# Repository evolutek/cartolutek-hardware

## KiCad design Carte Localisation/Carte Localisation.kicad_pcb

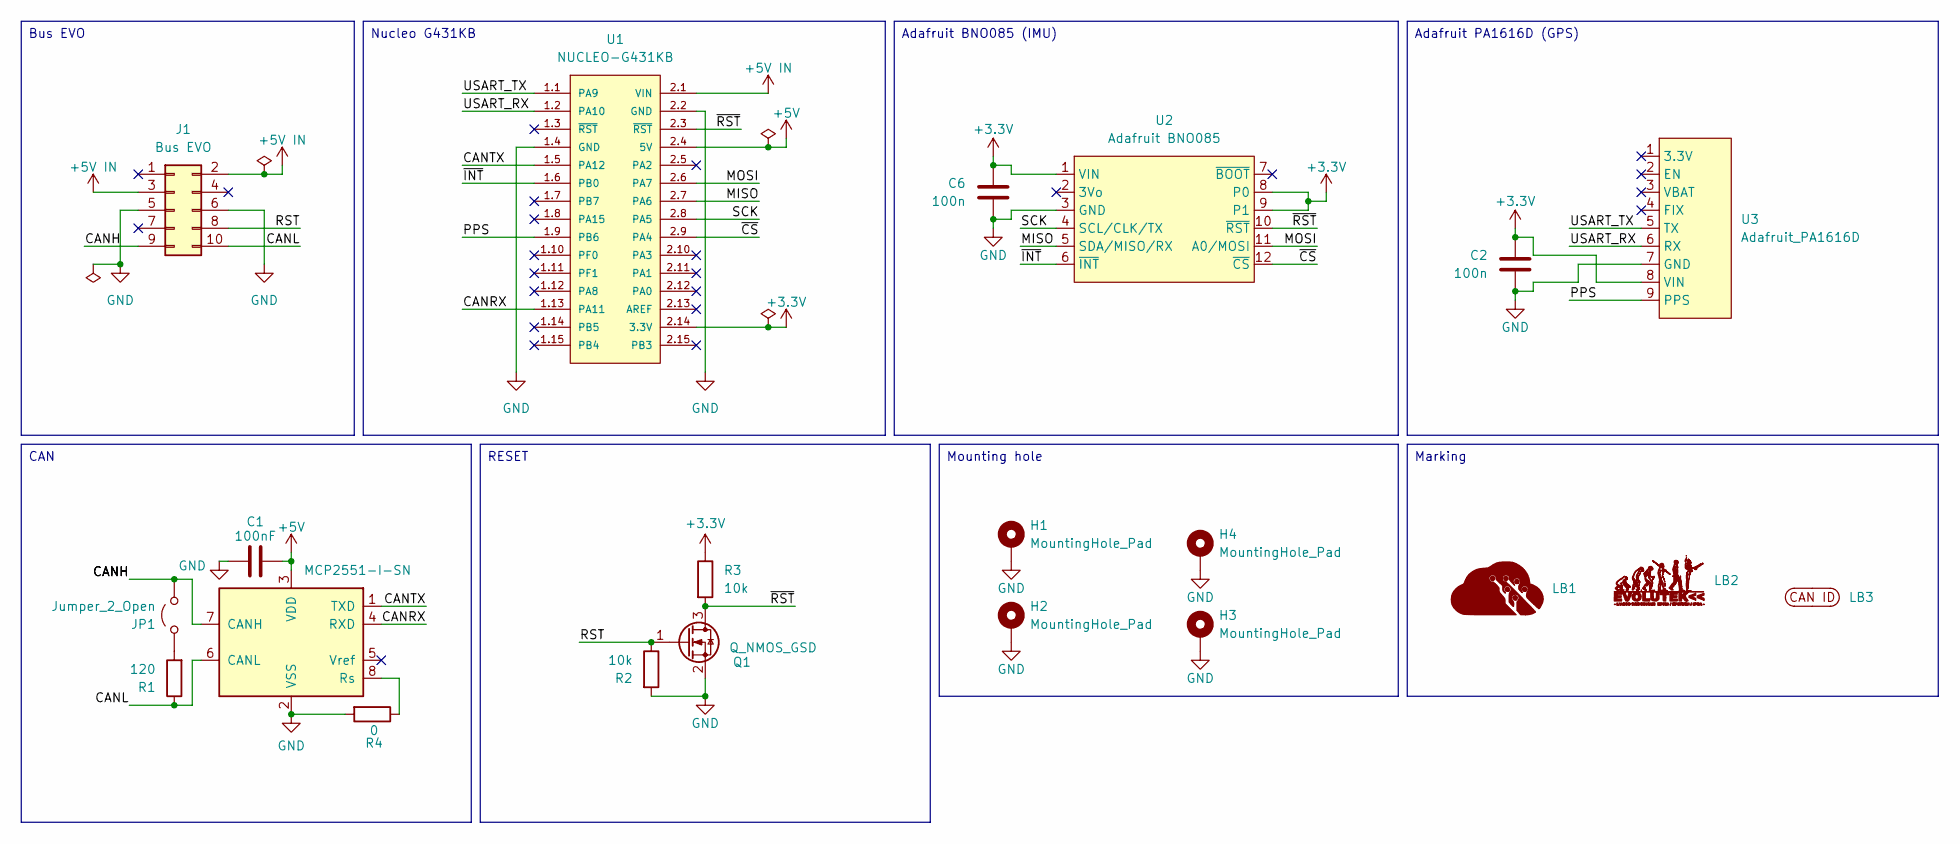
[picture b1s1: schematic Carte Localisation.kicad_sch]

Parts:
C1: 100nF; C_0603_1608Metric
C2, C6: 100n; C_0603_1608Metric
H1, H2, H3, H4: MountingHole_Pad; MountingHole_3.2mm_M3_Pad_Via
J1: Bus EVO; 690367281076
JP1: Jumper_2_Open; PinHeader_1x02_P2.54mm_Vertical
LB1: LOGO; Logo Aisler Min
LB2: LOGO; logo-evo-min
LB3: CAN ID Label
Q1: Q_NMOS_GSD; SOT-23
R1: 120; R_0603_1608Metric
R2, R3: 10k; R_0603_1608Metric
R4: 0; R_0603_1608Metric
U1: NUCLEO-G431KB; MODULE_NUCLEO-32
U2: Adafruit BNO085
U3: Adafruit_PA1616D; Adafruit PA1616D
U4: MCP2551-I-SN; SOIC-8_3.9x4.9mm_P1.27mm

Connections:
+3.3V: C2.2, C6.2, R3.1, U1.2.14 (3.3V), U2.1 (VIN), U2.8 (P0), U2.9 (P1), U3.8 (VIN)
+5V: C1.1, U1.2.4 (5V), U4.3 (VDD)
+5V IN: J1.2, J1.3, U1.2.1 (VIN)
/CANH: J1.9, JP1.2 (B), U4.7 (CANH)
/CANL: J1.10, R1.1, U4.6 (CANL)
/CANRX: U1.1.13 (PA11), U4.4 (RXD)
/CANTX: U1.1.5 (PA12), U4.1 (TXD)
/MISO: U1.2.7 (PA6), U2.5 (SDA/MISO/RX)
/MOSI: U1.2.6 (PA7), U2.11 (A0/MOSI)
/PPS: U1.1.9 (PB6), U3.9 (PPS)
/RST: J1.8, Q1.1 (G), R2.1
/SCK: U1.2.8 (PA5), U2.4 (SCL/CLK/TX)
/USART_RX: U1.1.2 (PA10), U3.6 (RX)
/USART_TX: U1.1.1 (PA9), U3.5 (TX)
/~CS: U1.2.9 (PA4), U2.12 (~CS)
/~INT: U1.1.6 (PB0), U2.6 (~INT)
/~RST: Q1.3 (D), R3.2, U1.2.3 (~RST), U2.10 (~RST)
GND: C1.2, C2.1, C6.1, H1.1, H2.1, H3.1, H4.1, J1.5, J1.6, Q1.2 (S), R2.2, R4.2, U1.1.4 (GND), U1.2.2 (GND), U2.3 (GND), U3.7 (GND), U4.2 (VSS)
unnamed: JP1.1 (A), R1.2
unnamed: R4.1, U4.8 (Rs)

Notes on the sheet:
Bus EVO
Nucleo G431KB
Marking
RESET
Adafruit PA1616D (GPS)
Adafruit BNO085 (IMU)
CAN
Mounting hole

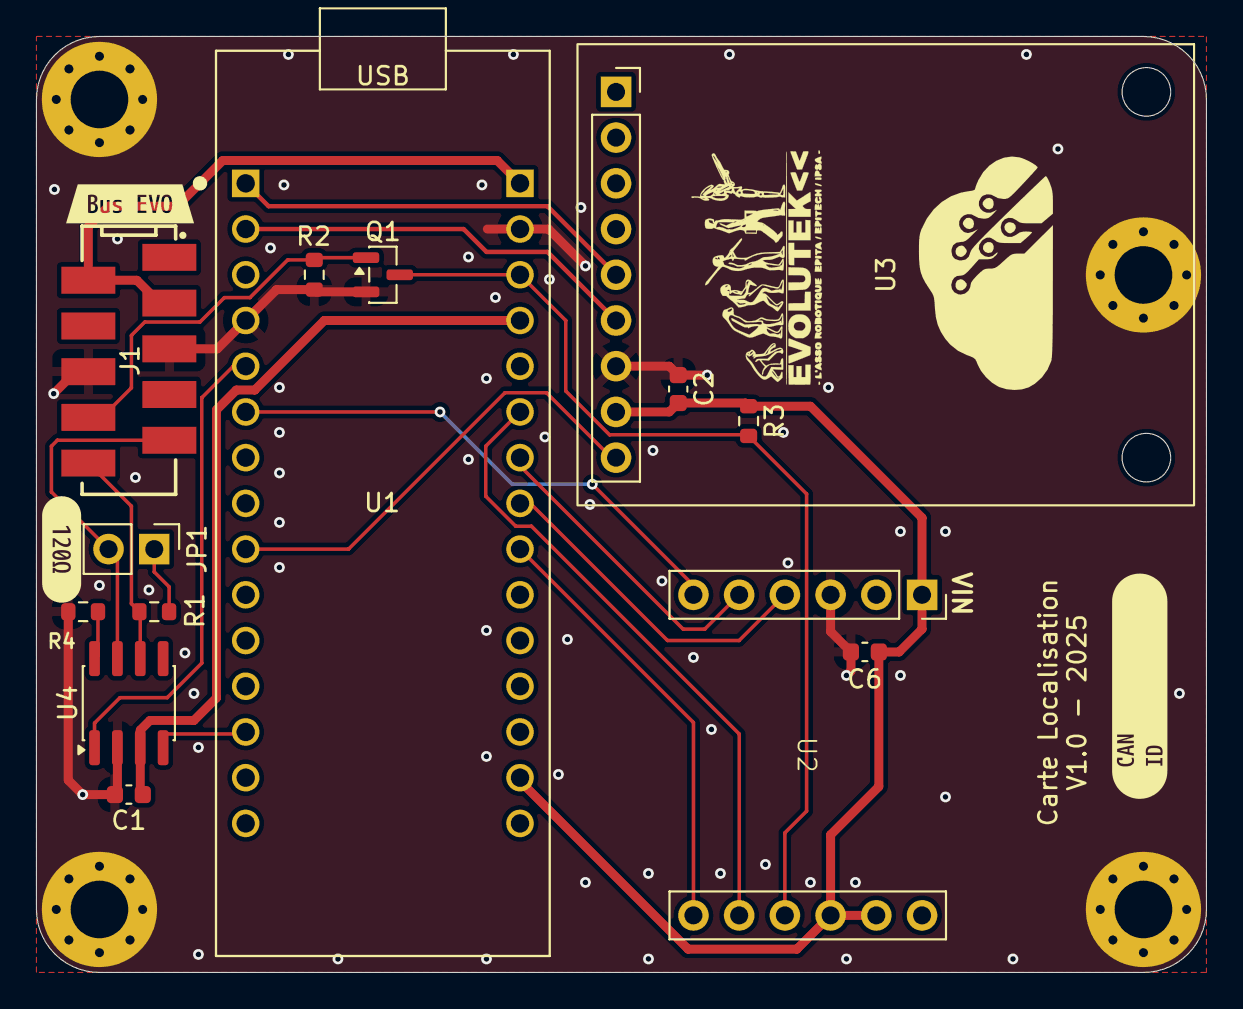
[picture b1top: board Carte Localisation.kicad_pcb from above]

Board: 2 copper layers, 65.0 x 52.0 mm, 23 parts (0 on the bottom side), 20 nets.

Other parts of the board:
kibuzzard-693DE181: G***; kibuzzard-693DE181
kibuzzard-693DE208: G***; kibuzzard-693DE208

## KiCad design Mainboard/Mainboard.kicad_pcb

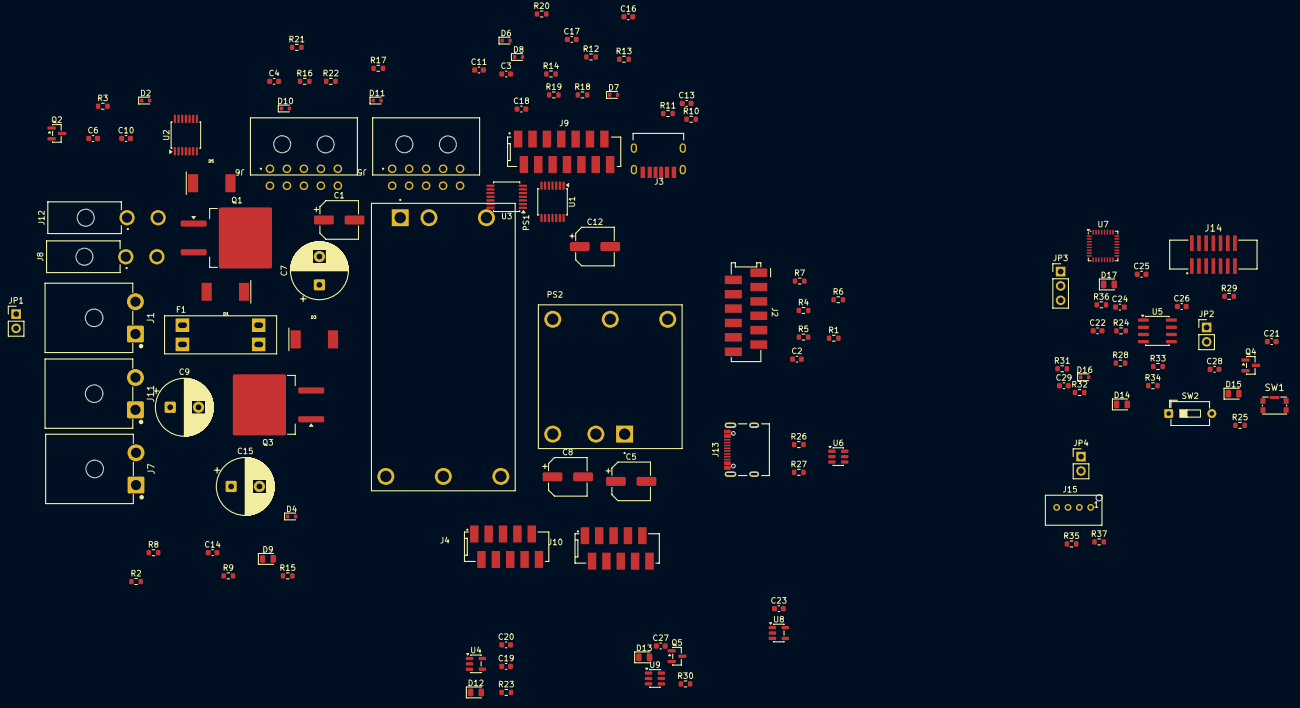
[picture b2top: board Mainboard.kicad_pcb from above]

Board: 2 copper layers, 121 parts (0 on the bottom side), 80 nets, no tracks yet.

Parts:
C1, C5, C8, C12: 100uF; CP_Elec_6.3x7.7
C2: 22nF; C_0603_1608Metric
C3, C4, C10, C11, C16, C17, C18, C21, C22, C23, C25, C26, C27: 100nF; C_0603_1608Metric
C6, C14, C19, C20: 1uF; C_0603_1608Metric
C7, C9, C15: 470uF; CP_Radial_D10.0mm_P5.00mm
C13, C24, C29: 10uF; C_0603_1608Metric
C28: 10nF; C_0603_1608Metric
D1, D3, D5: D; DO-214AB
D2, D4: 15V; D_SOD-523
D6, D7, D8, D10, D11, D16: 3V; D_SOD-523
D9, D12: RED; LED_0805_2012Metric
D13, D14, D15: YELLOW; LED_0805_2012Metric
D17: GREEN; LED_0805_2012Metric
F1: 50A; FUSE_3557-2
J1: BATT; 657002140101
J2: Computer Interface; J_Wurth_WR-MM_690367281276
J3: USB_C_Receptacle_PowerOnly_6P; GCT_USB4125-GF-A_REVA2
J4, J10: Bus EVO; 690367281076
J5, J6: Hoop Interface Front; 66201021022
J7, J11: MOTORS; 657002140101
J8, J12: AUX; 649002227222
J9: UI Interface; 690367281476
J13: USB_C_Receptacle_USB2.0_16P; 629722000214
J14: STLINK; 62701420621
J15: I2C; B04B-PASK
JP1, JP2, JP4: Jumper_2_Small_Open; PinHeader_1x02_P2.54mm_Vertical
JP3: Jumper_3_Bridged12; PinHeader_1x03_P2.54mm_Vertical
PS1: TEN_40-4812WIE; TRACO_CONV_TEN
PS2: THL_20-2411WI; TRACO_CONV_THL
Q1, Q3: Q_PMOS_GDS; TO-263-2
Q2: Q_NMOS_GSD 60V; SOT-23
Q4, Q5: NMOS; SOT-23
R1, R2, R5, R6, R7, R8, R10, R11, R12, R13, R14, R21, R22, R25, R29, R31: 10k; R_0603_1608Metric
R3, R9, R16, R17, R18, R19, R20: 33k; R_0603_1608Metric
R4, R15: 22k; R_0603_1608Metric
R23, R30, R32, R33, R34, R36: 510; R_0603_1608Metric
R24: 120; R_0603_1608Metric
R26, R27: 5.1k; R_0603_1608Metric
R28: 0; R_0603_1608Metric
R35, R37: 4.7k; R_0603_1608Metric
SW1: 435431019840
SW2: SW_DIP_x01; SW_DIP_SPSTx01_Slide_6.7x4.1mm_W7.62mm_P2.54mm_LowProfile
U1, U2, U3: SN74LVTH125; TSSOP-14_4.4x5mm_P0.65mm
U4: NCP718xSN330; SOT-23-5
U5: MCP2551-I-SN; SOIC-8_3.9x4.9mm_P1.27mm
U6: WE-TVS-82400102; SOT-23-6
U7: STM32G491KEUx; QFN-32-1EP_5x5mm_P0.5mm_EP3.45x3.45mm-Without thermal pad
U8: SN74LVC1G32; SOT-23-5
U9: SN74LVC1G11; SOT-23-6

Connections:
+3.3V: C3.1, C4.1, C11.1, C20.1, C23.1, C24.1, C25.1, C26.1, C27.1, C28.1, D12.2 (A), J14.3, JP3.3 (B), R25.1, R30.1, R35.1, R37.1, SW2.1, U1.14 (VCC), U2.14 (VCC), U3.14 (VCC), U4.5 (OUT), U7.1 (VDD), U7.15 (VDDA), U7.17 (VDD), U8.5 (VCC), U9.5 (VCC)
+5V: C13.1, C19.1, C22.1, J2.1, J2.2, J3.A9 (VBUS), J3.B9 (VBUS), J4.2, J4.3, J10.2, J10.3, JP4.1 (A), R10.2, R11.2, U4.1 (IN), U4.3 (EN), U5.3 (VDD)
+5VT: C12.1, PS2.3 (+VOUT)
+12V: C5.1, C8.1, J4.1, J5.7, J6.7, J9.2, J10.1, PS1.4 (+VOUT), PS2.1 (+VIN(VCC))
/Interfaces/AUTO_MODE_ENABLE: D14.2 (A), U1.5 (2A), U7.12 (PA7)
/Interfaces/AUTO_MODE_ENABLE_U: J9.8, U1.6 (2Y)
/Interfaces/AUTO_MODE_SWITCH: C17.1, D7.1 (K), R13.1, R19.1, U7.26 (PB3)
/Interfaces/BUZZER: U3.2 (1A), U7.9 (PA4)
/Interfaces/BUZZER_U: J9.12, U3.3 (1Y)
/Interfaces/CAMERA_SYNC_C: C2.1, J2.7, R4.1, U2.12 (4A)
/Interfaces/CAMERA_SYNC_H: J5.5, J6.5, U2.11 (4Y)
/Interfaces/CANH: J2.11, J4.9, J10.9, JP2.1 (A), U5.7 (CANH)
/Interfaces/CANL: J2.12, J4.10, J10.10, R24.2, U5.6 (CANL)
/Interfaces/EMERGENCY_STOP: D13.1 (K), J4.7, J10.7, Q5.1 (D), U7.6 (PA1)
/Interfaces/EMERGENCY_SWITCH_BACK: D11.1 (K), R17.2, R22.1, U9.3 (B)
/Interfaces/EMERGENCY_SWITCH_FRONT: D10.1 (K), R16.2, R21.1, U9.1 (A)
/Interfaces/GREEN_LED_C: J2.5, R5.1, U1.12 (4A)
/Interfaces/GREEN_LED_U: J9.10, U1.11 (4Y)
/Interfaces/HEADLIGHTS: U3.12 (4A), U7.10 (PA5)
/Interfaces/HEADLIGHTS_H: J5.8, J6.8, U3.11 (4Y)
/Interfaces/LEDSTRIP_BACK: U2.9 (3A), U7.30 (PB7)
/Interfaces/LEDSTRIP_BACK_H: J6.4, U2.8 (3Y)
/Interfaces/LEDSTRIP_FRONT: U2.5 (2A), U7.27 (PB4)
/Interfaces/LEDSTRIP_FRONT_H: J5.4, U2.6 (2Y)
/Interfaces/MOTOR_POWER_ENABLE: D15.2 (A), JP3.2 (C), Q2.1 (G), U1.2 (1A)
/Interfaces/MOTOR_POWER_ENABLE_U: J9.6, U1.3 (1Y)
/Interfaces/MOTOR_POWER_SWITCH: C16.1, D6.1 (K), R12.1, R18.1, U7.13 (PB0)
/Interfaces/RED_LED_C: J2.6, R6.1, U1.9 (3A)
/Interfaces/RED_LED_U: J9.11, U1.8 (3Y)
/Interfaces/RESET_SOFT: J2.9, R1.1, U8.2 (B)
/Interfaces/RESET_SWITCH: C18.1, D8.1 (K), R14.1, R20.1, U8.1 (A)
/Interfaces/SCL: J9.14, J15.3, R35.2, U7.19 (PA9)
/Interfaces/SDA: J9.13, J15.2, R37.2, U7.18 (PA8)
/Interfaces/WARNING_LIGHTS: U2.2 (1A), U7.25 (PA15)
/Interfaces/WARNING_LIGHTS_H: J5.9, J6.9, U2.3 (1Y)
/Interfaces/~EMERGENCY_STOP_SOFT: J2.8, R7.1, U9.6 (C)
/Interfaces/~POWER_SWITCH: C6.2, D2.2 (A), J9.3, JP1.2 (B), Q1.1 (G), R2.2, R3.1
/Logic/BATTERY_SENSE: C29.1, D16.1 (K), R31.2, R32.1, U7.5 (PA0)
/Logic/CAN_RX: U5.4 (RXD), U7.28 (PB5)
/Logic/CAN_TX: U5.1 (TXD), U7.29 (PB6)
/Logic/D_N: J13.A7 (D-), J13.B7 (D-), U6.1
/Logic/D_P: J13.A6 (D+), J13.B6 (D+), U6.3
/Logic/RST: J2.10, J4.8, J10.8, Q4.2 (G), U8.4 (S)
/Logic/STATUS: D17.2 (A), U7.20 (PA10)
/Logic/SWCLK: J14.6, U7.24 (PA14)
/Logic/SWDIO: J14.4, U7.23 (PA13)
/Logic/USB_N: U6.6, U7.21 (PA11)
/Logic/USB_P: U6.4, U7.22 (PA12)
/Logic/VCP_RX: J14.13, U7.8 (PA3)
/Logic/VCP_TX: J14.14, U7.7 (PA2)
/Logic/~RST: C21.1, J14.12, Q4.1 (D), R25.2, SW1.4, U7.4 (PG10)
GND: C1.2, C2.2, C3.2, C4.2, C5.2, C7.2, C8.2, C9.2, C10.2, C11.2, C12.2, C13.2, C15.2, C16.2, C17.2, C18.2, C19.2, C20.2, C21.2, C22.2, C23.2, C24.2, C25.2, C26.2, C27.2, C28.2, C29.2, D1.2 (A), D6.2 (A), D7.2 (A), D8.2 (A), D10.2 (A), D11.2 (A), D16.2 (A), J1.2, J2.3, J2.4, J3.A12 (GND), J3.B12 (GND), J3.S1 (SHIELD), J4.5, J4.6, J5.2, J5.3, J6.2, J6.3, J7.2, J8.2, J9.4, J10.5, J10.6, J11.2, J12.2, J13.A1 (GND), J13.A12 (GND), J13.B1 (GND), J13.B12 (GND), J13.S1 (SHIELD), J14.5, J14.7, J14.11, J15.4, JP1.1 (A), PS1.2 (-VIN(GND)), PS1.5 (-VOUT), PS2.2 (-VIN(GND)), PS2.5 (-VOUT), Q2.2 (S), Q4.3 (S), Q5.3 (S), R1.2, R3.2, R4.2, R5.2, R6.2, R7.2, R12.2, R13.2, R14.2, R15.2, R21.2, R22.2, R23.2, R26.1, R27.2, R28.2, R29.2, R32.2, R33.2, R34.2, R36.2, SW1.3, SW1.SH, U1.7 (GND), U2.7 (GND), U3.7 (GND), U4.2 (GND), U5.2 (VSS), U6.2, U7.14 (VSSA), U7.16 (VSS), U7.32 (VSS), U8.3 (GND), U9.2 (GND)
unnamed: C14.2, D4.2 (A), Q3.1 (G), R8.2, R9.1
unnamed: D9.1 (K), R15.1
unnamed: D12.1 (K), R23.1
unnamed: D13.2 (A), R30.2
unnamed: D14.1 (K), R33.1
unnamed: D15.1 (K), R34.1
unnamed: D17.1 (K), R36.1
unnamed: F1.1, J1.1
unnamed: J3.A5 (CC1), R10.1
unnamed: J3.B5 (CC2), R11.1
unnamed: J5.10, R16.1
unnamed: J6.10, R17.1
unnamed: J9.5, R18.2
unnamed: J9.7, R19.2
unnamed: J9.9, R20.2
unnamed: J13.A5 (CC1), R26.2
unnamed: J13.B5 (CC2), R27.1
unnamed: J15.1, JP4.2 (B)
unnamed: JP2.2 (B), R24.1
unnamed: JP3.1 (A), U7.11 (PA6)
unnamed: Q2.3 (D), R9.2
unnamed: Q5.2 (G), U9.4
unnamed: R28.1, U5.8 (Rs)
unnamed: R29.1, SW2.2, U7.31 (PB8)
VBAT: C6.1, C14.1, D1.1 (K), D2.1 (K), D3.1 (K), D4.1 (K), D5.1 (K), F1.2, Q1.3 (S), Q3.3 (S), R2.1, R8.1
VBUS: J13.A4 (VBUS), J13.A9 (VBUS), J13.B4 (VBUS), J13.B9 (VBUS), U6.5
VCC: C1.1, C7.1, C10.1, D3.2 (A), J5.1, J5.6, J6.1, J6.6, J8.1, J9.1, J12.1, PS1.1 (+VIN(VCC)), Q1.2 (D), R31.1
VPP: C9.1, C15.1, D5.2 (A), D9.2 (A), J7.1, J11.1, Q3.2 (D)

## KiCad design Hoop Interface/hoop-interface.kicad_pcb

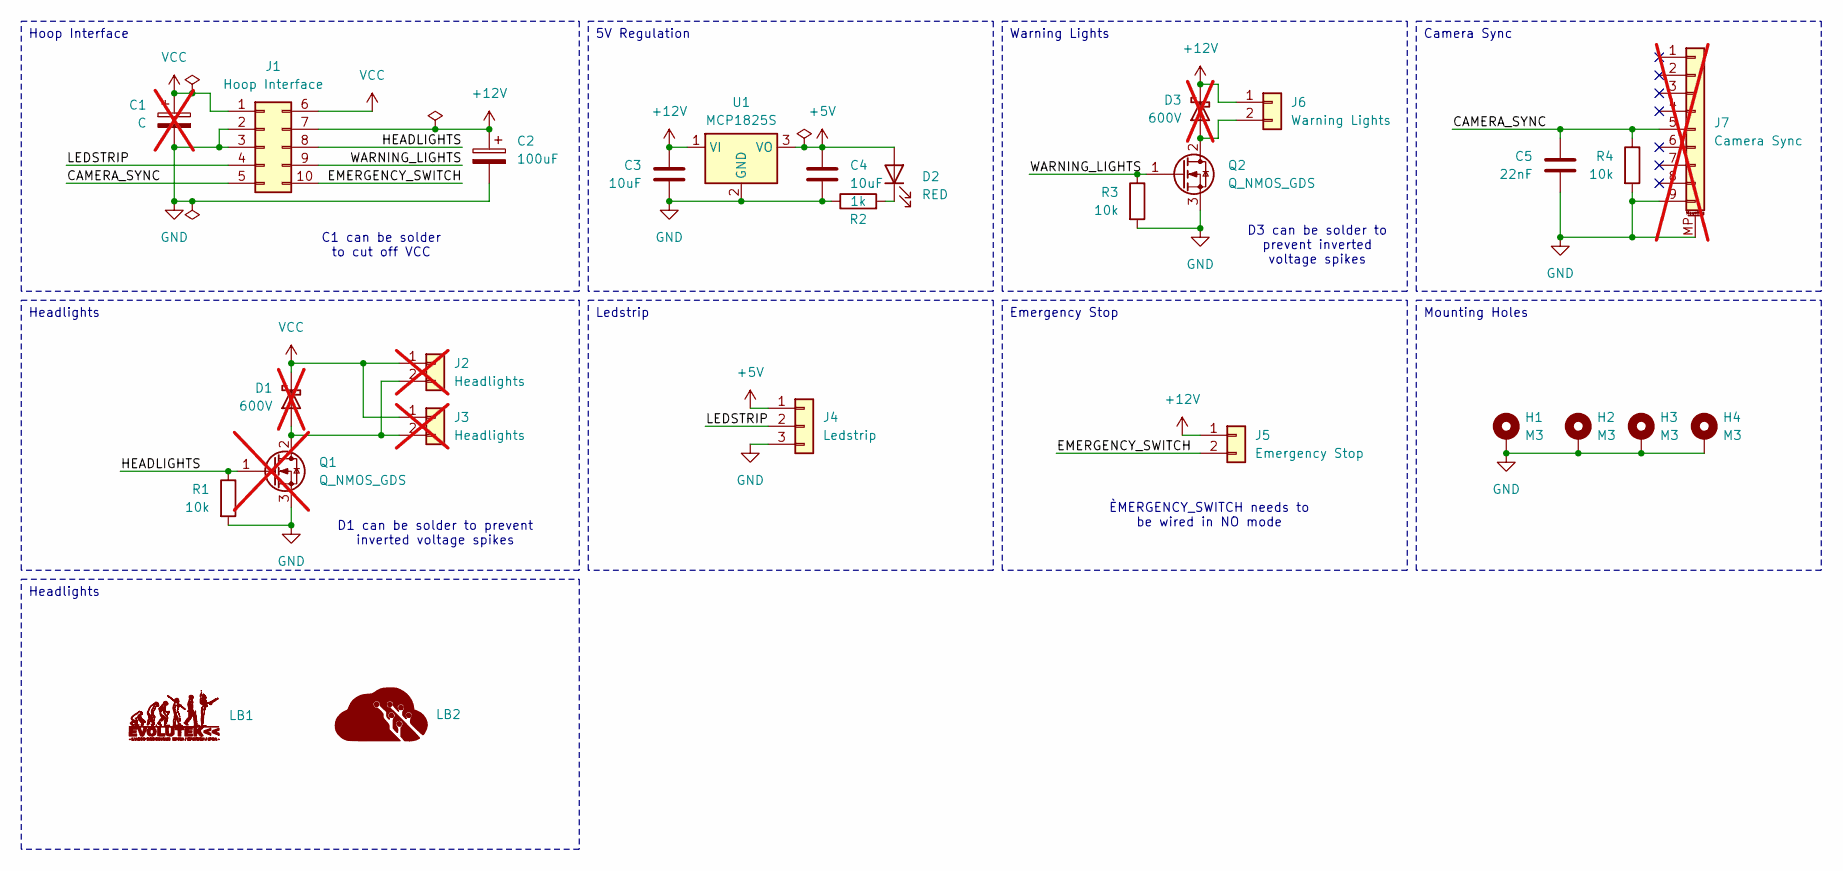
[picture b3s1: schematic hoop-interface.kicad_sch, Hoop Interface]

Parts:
C1: C; CP_Radial_D10.0mm_P5.00mm; not fitted
C2: 100uF; CP_Elec_6.3x7.7
C3, C4: 10uF; C_0603_1608Metric
C5: 22nF; C_0603_1608Metric
D1, D3: 600V; D_SMB; not fitted
D2: RED; LED_0805_2012Metric
H1, H2, H3, H4: M3; MountingHole_3.2mm_M3_Pad_Via
J1: Hoop Interface; 66201021022
J2, J3: Headlights; 66200221022; not fitted
J4: Ledstrip; B03B-PASK
J5: Emergency Stop; 66200221022
J6: Warning Lights; 66200221022
J7: Camera Sync; JST_SH_BM09B-SRSS-TB_1x09-1MP_P1.00mm_Vertical; not fitted
LB1: LOGO; logo-evo-micro
LB2: LOGO; Logo Aisler Micro
Q1: Q_NMOS_GDS; SOT-223-3_TabPin2; not fitted
Q2: Q_NMOS_GDS; SOT-223-3_TabPin2
R1, R3, R4: 10k; R_0603_1608Metric
R2: 1k; R_0603_1608Metric
U1: MCP1825S; SOT-223-3_TabPin2

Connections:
+5V: C4.1, D2.2 (A), J4.1, U1.3 (VO)
+12V: C2.1, C3.1, D3.1 (K), J1.7, J5.1, J6.1, U1.1 (VI)
/CAMERA_SYNC: C5.1, J1.5, J7.5, R4.1
/EMERGENCY_STOP: J1.10, J5.2
/HEADLIGHTS: J1.8, Q1.1 (G), R1.1
/LEDSTRIP: J1.4, J4.2
/WARNING_LIGHTS: J1.9, Q2.1 (G), R3.1
GND: C1.2, C2.2, C3.2, C4.2, C5.2, H1.1, H2.1, H3.1, H4.1, J1.2, J1.3, J4.3, J7.9, J7.MP (MountPin), Q1.3 (S), Q2.3 (S), R1.2, R2.1, R3.2, R4.2, U1.2 (GND)
unnamed: D1.2 (A), J2.2, J3.2, Q1.2 (D)
unnamed: D2.1 (K), R2.2
unnamed: D3.2 (A), J6.2, Q2.2 (D)
VCC: C1.1, D1.1 (K), J1.1, J1.6, J2.1, J3.1

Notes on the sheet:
D1 can be solder to prevent inverted voltage spikes
C1 can be solder to cut off VCC
ÈMERGENCY_SWITCH needs to be wired in NO mode
D3 can be solder to prevent inverted voltage spikes
Emergency Stop
Ledstrip
Warning Lights
5V Regulation
Headlights
Mounting Holes
Hoop Interface
Camera Sync

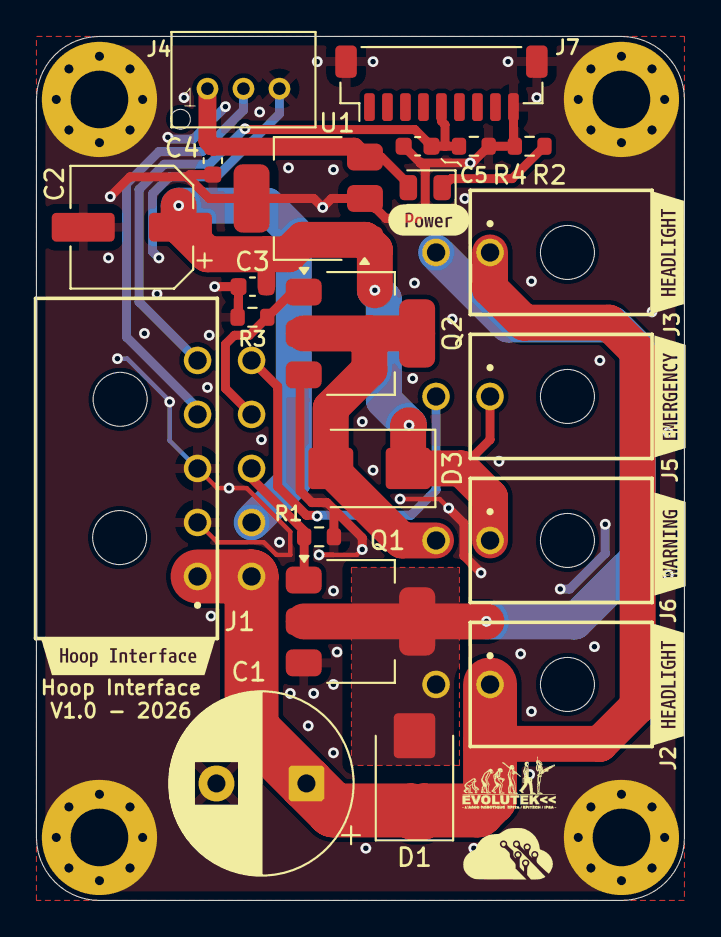
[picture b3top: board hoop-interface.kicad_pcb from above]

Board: 2 copper layers, 36.0 x 48.0 mm, 34 parts (0 on the bottom side), 12 nets.

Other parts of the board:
kibuzzard-69584B36: G***; kibuzzard-69584B36
kibuzzard-69584B63, kibuzzard-69584B63#2: G***; kibuzzard-69584B63
kibuzzard-69584B83: G***; kibuzzard-69584B83
kibuzzard-69584BC4: G***; kibuzzard-69584BC4
kibuzzard-69584D60: G***; kibuzzard-69584D60

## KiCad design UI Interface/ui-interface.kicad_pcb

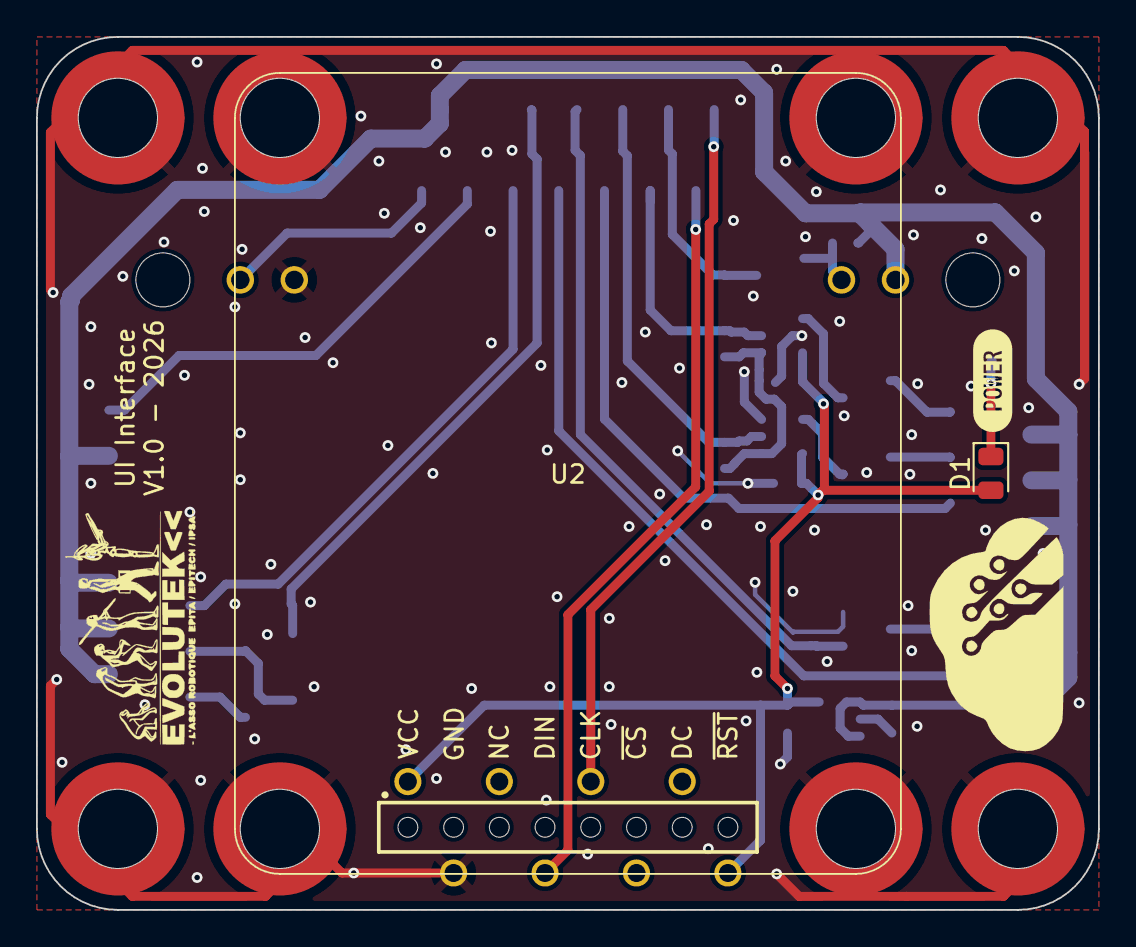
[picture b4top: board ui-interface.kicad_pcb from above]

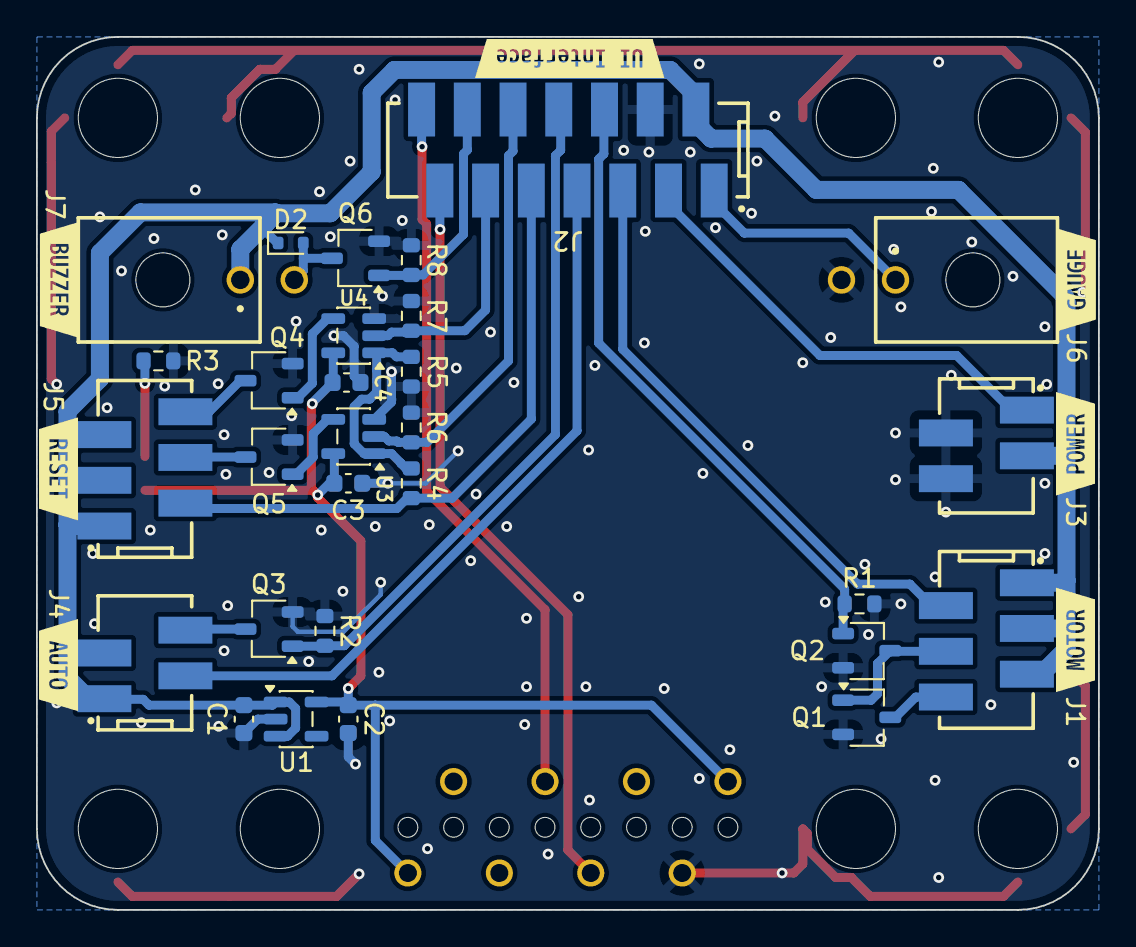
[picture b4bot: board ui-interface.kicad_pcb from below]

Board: 2 copper layers, 59.0 x 48.5 mm, 45 parts (36 on the bottom side), 25 nets.

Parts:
C1, C2: 1uF; C_0603_1608Metric
C3, C4: 100nF; C_0603_1608Metric
D1: RED; LED_0805_2012Metric
D2: D_Schottky; D_SOD-523
H1, H2, H3, H4: M3; WA-SMSI_9774110360
J1: Motor Power Switch; 690367280676
J2: UI Interface; 690367281476
J3: Power Switch; 690367280476
J4: Auto Mode Switch; 690367280476
J5: Reset Switch; 690367280676
J6: Battery Gauge; 66200221022
J7: Buzzer; 66200221022
LB1: LOGO; Logo Aisler Min
LB2: LOGO; logo-evo-min
Q1, Q2, Q3, Q4, Q5, Q6: Q_NMOS_GSD; TSOT-23
R1, R2, R5, R6, R7, R8: 10k; R_0603_1608Metric
R3: 510; R_0603_1608Metric
R4: 33k; R_0603_1608Metric
U1: NCP718xSN330; SOT-23-5
U2: Waveshare_1.5_inch_OLED; Waveshare 1.5 inch with 8mm spacers
U3, U4: SN74LVC1G32; SOT-23-5
kibuzzard-69598A88: G***; kibuzzard-69598A88
kibuzzard-69598DA4: G***; kibuzzard-69598DA4
kibuzzard-695995E5: G***; kibuzzard-695995E5
kibuzzard-695995F9: G***; kibuzzard-695995F9
kibuzzard-6959960F: G***; kibuzzard-6959960F
kibuzzard-69599623: G***; kibuzzard-69599623
kibuzzard-69599634: G***; kibuzzard-69599634
kibuzzard-69599736: G***; kibuzzard-69599736

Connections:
+3.3V: C2.1, C3.1, C4.1, D1.2 (A), U1.5 (OUT), U2.1 (VCC), U2.8 (~RST), U3.5 (VCC), U4.5 (VCC)
+12V: C1.1, D2.1 (K), J1.1, J1.3, J1.5, J2.2, J3.3, J4.1, J4.3, J5.1, J5.3, J5.5, J7.1, U1.1 (IN), U1.3 (EN)
/AUTO_MODE_ENABLE: J2.8, Q3.1 (G), R2.1
/AUTO_MODE_SWITCH: J2.7, J4.2
/BUZZER: J2.12, Q6.1 (G), R8.1
/GREEN: J1.4, Q1.1 (G), Q2.3 (D)
/GREEN_LED: J2.10, R6.1, U3.2 (B)
/MOTOR_POWER_ENABLE: J2.6, Q2.1 (G), R1.1
/MOTOR_POWER_SWITCH: J1.2, J2.5
/RED: J1.6, Q1.3 (D)
/RED_LED: J2.11, R7.1, U4.2 (B)
/RESET: J2.9, J5.2, R4.1
/SCL: J2.14, U2.5 (CLK)
/SDA: J2.13, U2.4 (DIN)
/~POWER_SWITCH: J2.3, J3.1
GND: C1.2, C2.2, C3.2, C4.2, H1.1, H2.1, H3.1, H4.1, J2.4, J3.2, J3.4, J6.2, Q1.2 (S), Q2.2 (S), Q3.2 (S), Q4.2 (S), Q5.2 (S), Q6.2 (S), R1.2, R2.2, R3.2, R5.2, R6.2, R7.2, R8.2, U1.2 (GND), U2.2 (GND), U2.MP, U3.3 (GND), U4.3 (GND)
unnamed: D1.1 (K), R3.1
unnamed: D2.2 (A), J7.2, Q6.3 (D)
unnamed: J4.4, Q3.3 (D)
unnamed: J5.4, Q5.3 (D)
unnamed: J5.6, Q4.3 (D)
unnamed: Q4.1 (G), U4.4 (S)
unnamed: Q5.1 (G), U3.4 (S)
unnamed: R4.2, R5.1, U3.1 (A), U4.1 (A)
VCC: J2.1, J6.1

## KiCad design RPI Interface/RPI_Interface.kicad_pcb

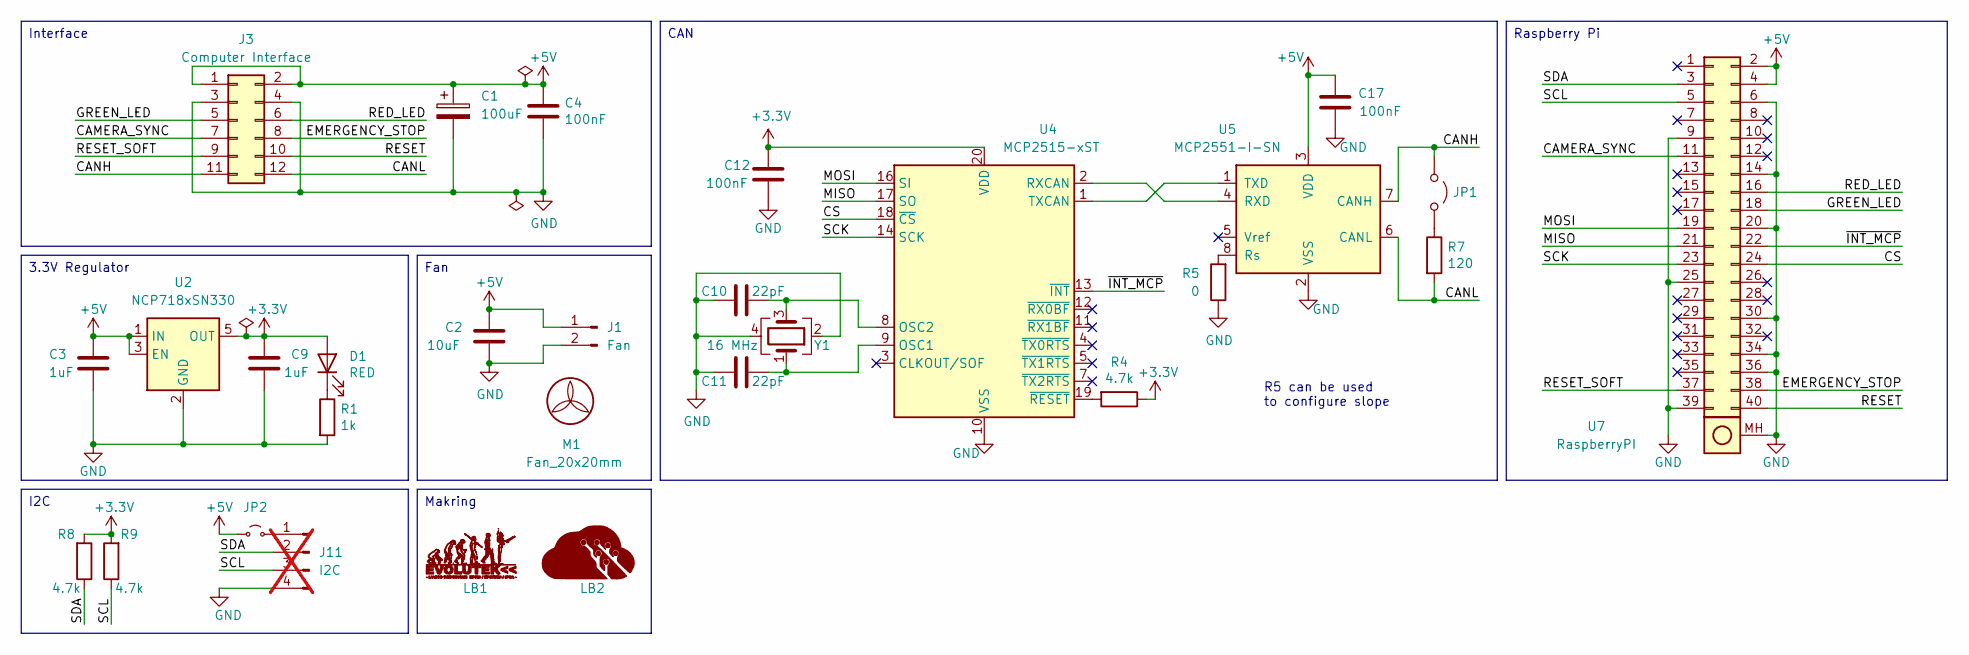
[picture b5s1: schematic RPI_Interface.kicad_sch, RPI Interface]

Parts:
C1: 100uF; CP_Elec_6.3x7.7
C2: 10uF; C_0603_1608Metric
C3, C9: 1uF; C_0603_1608Metric
C4, C12, C17: 100nF; C_0603_1608Metric
C10, C11: 22pF; C_0603_1608Metric
D1: RED; LED_0805_2012Metric
J1: Fan; JST_XH_B2B-XH-AM_1x02_P2.50mm_Vertical
J3: Computer Interface; J_Wurth_WR-MM_690367281276
J11: I2C; B04B-PASK; not fitted
JP1: Jumper_2_Open; PinHeader_1x02_P2.54mm_Vertical
JP2: Jumper_2_Small_Open; PinHeader_1x02_P2.54mm_Vertical
LB1: LOGO; logo-evo-micro
LB2: LOGO; Logo Aisler Micro
M1: Fan_20x20mm; 40x40x10_DC_FAN
R1: 1k; R_0603_1608Metric
R4, R8, R9: 4.7k; R_0603_1608Metric
R5: 0; R_0603_1608Metric
R7: 120; R_0603_1608Metric
U2: NCP718xSN330; SOT-23-5
U4: MCP2515-xST; TSSOP-20_4.4x6.5mm_P0.65mm
U5: MCP2551-I-SN; SOIC-8_3.9x4.9mm_P1.27mm
U7: RaspberryPI; Shield_Raspberry_Pi_with_11mm_Header
Y1: 16 MHz; Crystal_SMD_5032-4Pin_5.0x3.2mm

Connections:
+3.3V: C9.1, C12.1, D1.2 (A), R4.1, R8.2, R9.2, U2.5 (OUT), U4.20 (VDD)
+5V: C1.1, C2.1, C3.1, C4.1, C17.2, J1.1, J3.1, J3.2, JP2.1 (A), U2.1 (IN), U2.3 (EN), U5.3 (VDD), U7.2, U7.4
/CAMERA_SYNC: J3.7, U7.11
/CANH: J3.11, JP1.1 (A), U5.7 (CANH)
/CANL: J3.12, R7.2, U5.6 (CANL)
/CS: U4.18 (~CS), U7.24
/GREEN_LED: J3.5, U7.18
/MISO: U4.17 (SO), U7.21
/MOSI: U4.16 (SI), U7.19
/RED_LED: J3.6, U7.16
/RESET: J3.10, U7.40
/RESET_SOFT: J3.9, U7.37
/SCK: U4.14 (SCK), U7.23
/SCL: J11.3, R9.1, U7.5
/SDA: J11.2, R8.1, U7.3
/~INT_MCP: U4.13 (~INT), U7.22
GND: C1.2, C2.2, C3.2, C4.2, C9.2, C10.2, C11.2, C12.2, C17.1, J1.2, J3.3, J3.4, J11.4, R1.2, R5.1, U2.2 (GND), U4.10 (VSS), U5.2 (VSS), U7.6, U7.9, U7.14, U7.20, U7.25, U7.30, U7.34, U7.36, U7.39, U7.MH (MountingHoles), Y1.2, Y1.4
unnamed: D1.1 (K), R1.1
unnamed: J11.1, JP2.2 (B)
unnamed: JP1.2 (B), R7.1
unnamed: C11.1, U4.9 (OSC1), Y1.1
unnamed: C10.1, U4.8 (OSC2), Y1.3
unnamed: U4.2 (RXCAN), U5.4 (RXD)
unnamed: U4.1 (TXCAN), U5.1 (TXD)
unnamed: R4.2, U4.19 (~RESET)
unnamed: R5.2, U5.8 (Rs)

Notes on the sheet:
R5 can be used to configure slope
I2C
Interface
Fan
Makring
Raspberry Pi
3.3V Regulator
CAN

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
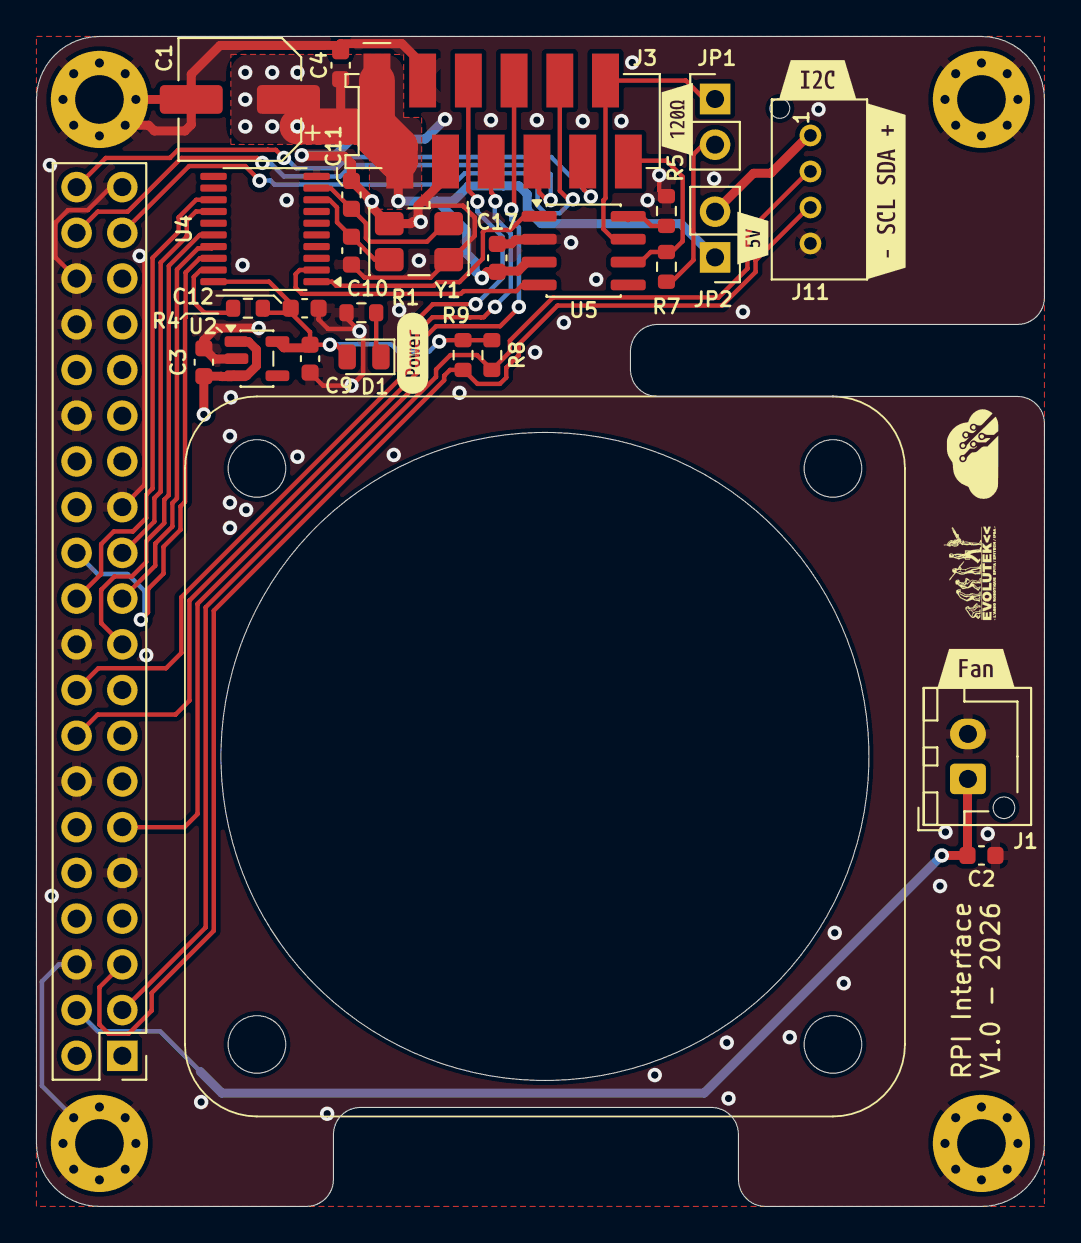
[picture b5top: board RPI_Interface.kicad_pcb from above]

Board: 2 copper layers, 56.0 x 65.0 mm, 35 parts (0 on the bottom side), 26 nets.

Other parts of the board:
kibuzzard-693864F8: G***; kibuzzard-693864F8
kibuzzard-693865CE: G***; kibuzzard-693865CE
kibuzzard-693865DC: G***; kibuzzard-693865DC
kibuzzard-693867AF: G***; kibuzzard-693867AF
kibuzzard-693867E9: G***; kibuzzard-693867E9
kibuzzard-69386806: G***; kibuzzard-69386806

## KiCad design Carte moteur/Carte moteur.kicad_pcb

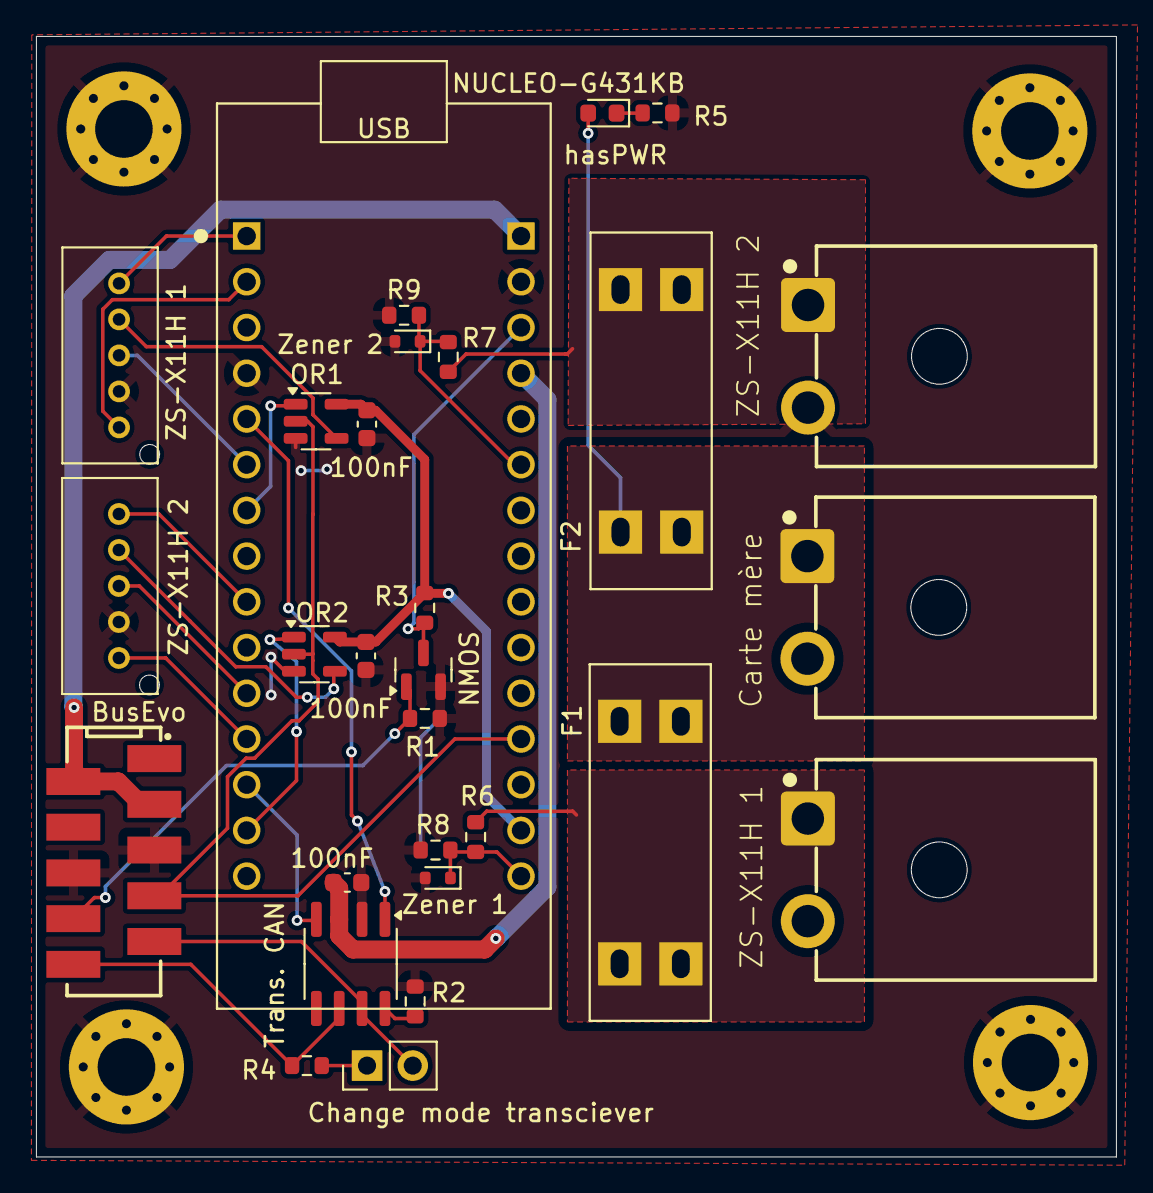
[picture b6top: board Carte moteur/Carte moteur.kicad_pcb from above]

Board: 2 copper layers, 60.0 x 62.2 mm, 33 parts (0 on the bottom side), 29 nets.

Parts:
100nF, 100nF#2, 100nF#3: 100nF; C_0603_1608Metric
BusEvo: Conn_02x05_Odd_Even; 690367281076
Carte mère: Conn_01x02_Pin; 657002140101
Change mode transciever: Jumper_2_Open; PinHeader_1x02_P2.54mm_Vertical
F1, F2: Fuse; FUSE_3557-2
H1, H2, H3, H4: M3; MountingHole_3.2mm_M3_Pad_Via
NMOS: Q_NMOS_GSD; SOT-23
NUCLEO-G431KB: NUCLEO-G431KB; MODULE_NUCLEO-32
OR1, OR2: SN74LVC1G32; SOT-23-5
R1, R3, R8, R9: 10k; R_0603_1608Metric
R2: 0; R_0603_1608Metric
R4: 120; R_0603_1608Metric
R5: 2.1k; R_0603_1608Metric
R6, R7: 100k; R_0603_1608Metric
Trans. CAN: MCP2551-I-SN; SOIC-8_3.9x4.9mm_P1.27mm
ZS-X11H 1, ZS-X11H 2: Conn_01x05_Pin; B05B-PASK
ZS-X11H 1#2, ZS-X11H 2#2: Conn_01x02_Pin; 657002140101
Zener 1, Zener 2: D_Zener; D_SOD-523
hasPWR: LED; LED_0603_1608Metric

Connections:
+3.3V: 100nF.1, 100nF#2.1, NUCLEO-G431KB.2.14 (3.3V), OR1.5 (VCC), OR2.5 (VCC), R3.1
+5V: 100nF#3.1, NUCLEO-G431KB.2.4 (5V), Trans. CAN.3 (VDD)
+5V IN: BusEvo.2, BusEvo.3, NUCLEO-G431KB.2.1 (VIN)
/AU: BusEvo.7, NUCLEO-G431KB.2.12 (PA0), OR1.2 (B), OR2.2 (B)
/BRAKE1: NUCLEO-G431KB.1.7 (PB7), OR1.1 (A)
/BRAKE2: NUCLEO-G431KB.1.14 (PB5), OR2.1 (A)
/CANH: BusEvo.9, Change mode transciever.2 (B), Trans. CAN.7 (CANH)
/CANL: BusEvo.10, R4.1, Trans. CAN.6 (CANL)
/CANRX: NUCLEO-G431KB.1.13 (PA11), Trans. CAN.4 (RXD)
/CANTX: NUCLEO-G431KB.1.5 (PA12), Trans. CAN.1 (TXD)
/DIR1: NUCLEO-G431KB.1.6 (PB0), ZS-X11H 1.3
/DIR2: NUCLEO-G431KB.1.11 (PF1), ZS-X11H 2.3
/PC1: NUCLEO-G431KB.2.15 (PB3), R6.1, R8.2, Zener 1.1 (K)
/PC2: NUCLEO-G431KB.2.6 (PA7), R7.1, R9.1, Zener 2.1 (K)
/RST: BusEvo.8, NMOS.1 (G), R1.1
/S1: NUCLEO-G431KB.1.1 (PA9), ZS-X11H 1.5
/S2: NUCLEO-G431KB.1.9 (PB6), ZS-X11H 2.5
/SPEED1: NUCLEO-G431KB.1.2 (PA10), ZS-X11H 1.1
/SPEED2: NUCLEO-G431KB.1.12 (PA8), ZS-X11H 2.1
/~RST: NMOS.3 (D), NUCLEO-G431KB.2.3 (~RST), R3.2
GND: 100nF.2, 100nF#2.2, 100nF#3.2, BusEvo.5, BusEvo.6, Carte mère.2, H1.1, H2.1, H3.1, H4.1, NMOS.2 (S), NUCLEO-G431KB.1.4 (GND), NUCLEO-G431KB.2.2 (GND), OR1.3 (GND), OR2.3 (GND), R1.2, R2.2, R5.1, R8.1, R9.2, Trans. CAN.2 (VSS), ZS-X11H 1.2, ZS-X11H 1#2.2, ZS-X11H 2.2, ZS-X11H 2#2.2, Zener 1.2 (A), Zener 2.2 (A)
unnamed: Carte mère.1, F1.1, F2.1, hasPWR.2 (A)
unnamed: R5.2, hasPWR.1 (K)
unnamed: OR1.4 (S), ZS-X11H 1.4
unnamed: OR2.4 (S), ZS-X11H 2.4
unnamed: F1.2, R6.2, ZS-X11H 1#2.1
unnamed: F2.2, R7.2, ZS-X11H 2#2.1
unnamed: Change mode transciever.1 (A), R4.2
unnamed: R2.1, Trans. CAN.8 (Rs)
